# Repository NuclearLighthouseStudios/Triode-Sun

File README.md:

# Triode Sun Tube Preamp

These are the KiCAD schematics and board layout filed for my Triode Sun Tube Preamp pedal.  
If you just want the Gerber files or a PDF of the schematic check out the releases tab for downloads.

This PCB should be easily manufacturable with most online PCB houses by just uploading the gerber files.

This board is designed to be used with my Switchboard Pedal IO PCB which you can find [here](https://github.com/NuclearLighthouseStudios/Switchboard).

## BOM

| Reference       | Quantity | Value  | Description                                          |
| :-------------- | -------: | -----: | :--------------------------------------------------- |
| C2 C4           | 2        | 470n   | WIMA MKS2 50V                                        |
| C1 C3 C5        | 3        | 100n   | WIMA MKS2 63V                                        |
| C6              | 1        | 1µ     | WIMA MKS2 50V                                        |
| J1              | 1        |        | Pin Header, 6 pins, 2.54mm spacing                   |
| J2              | 1        |        | DC Barrel Jack with internal switch                  |
| Q1 Q2           | 2        | BC547B | 0.1A Ic, 45V Vce, Small Signal NPN Transistor, TO-92 |
| R1 R2 R5 R9 R10 | 5        | 1M     | Metal film resistor 1%, DIN 0207                     |
| R3 R11          | 2        | 10k    | Metal film resistor 1%, DIN 0207                     |
| R4 R12          | 2        | 39k    | Metal film resistor 1%, DIN 0207                     |
| R6 R7           | 2        | 390K   | Metal film resistor 1%, DIN 0207                     |
| R8              | 1        | 100K   | Metal film resistor 1%, DIN 0207                     |
| RV1 RV2         | 2        | 100k   | Alps RK09K1130C94 Potentiometer                      |
| U1              | 1        | ECC82  | ECC82 / 17AU7 in noval print socket                  |

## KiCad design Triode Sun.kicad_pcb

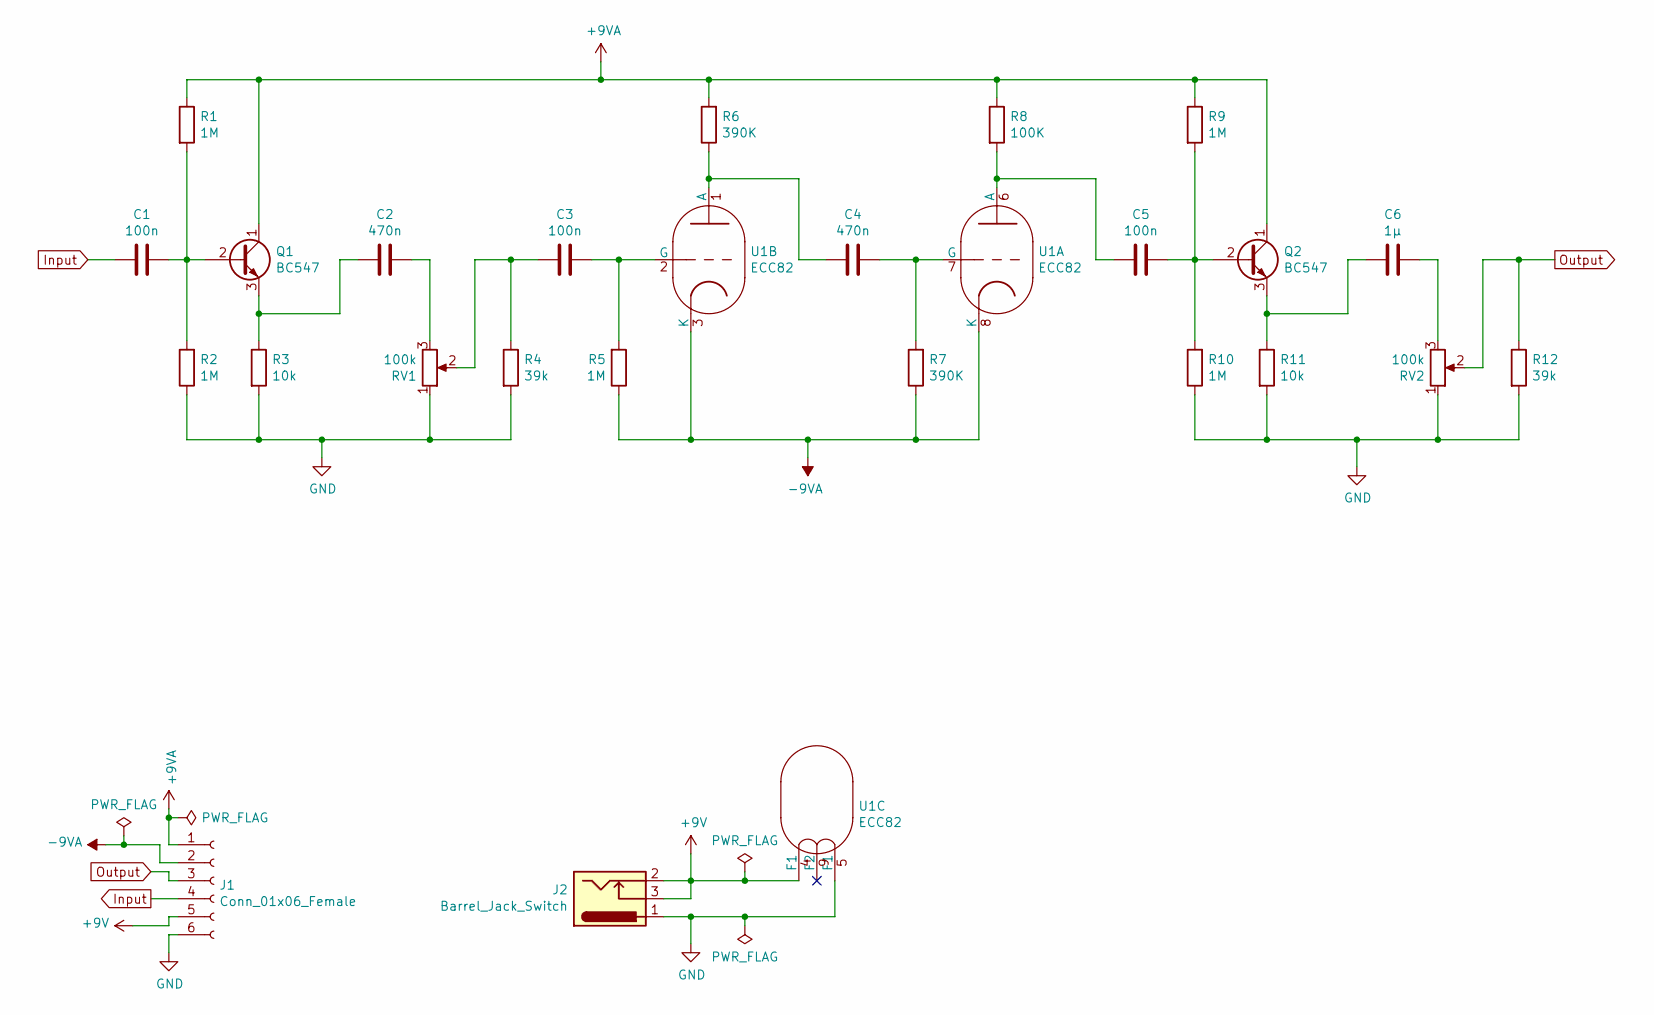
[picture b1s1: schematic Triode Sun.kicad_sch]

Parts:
C1, C3, C5: 100n; C_Rect_L7.2mm_W2.5mm_P5.00mm_FKS2_FKP2_MKS2_MKP2
C2, C4: 470n; C_Rect_L7.2mm_W3.5mm_P5.00mm_FKS2_FKP2_MKS2_MKP2
C6: 1µ; C_Rect_L7.2mm_W4.5mm_P5.00mm_FKS2_FKP2_MKS2_MKP2
J1: Conn_01x06_Female; PinHeader_1x06_P2.54mm_Vertical
J2: Barrel_Jack_Switch; BarrelJack_Horizontal_Short
Q1, Q2: BC547; TO-92_Wide
R1, R2, R5, R9, R10: 1M; R_Axial_DIN0207_L6.3mm_D2.5mm_P2.54mm_Vertical
R3, R11: 10k; R_Axial_DIN0207_L6.3mm_D2.5mm_P2.54mm_Vertical
R4, R12: 39k; R_Axial_DIN0207_L6.3mm_D2.5mm_P2.54mm_Vertical
R6, R7: 390K; R_Axial_DIN0207_L6.3mm_D2.5mm_P2.54mm_Vertical
R8: 100K; R_Axial_DIN0207_L6.3mm_D2.5mm_P2.54mm_Vertical
RV1, RV2: 100k; Potentiometer_Alps_RK09K_Single_Vertical
U1: ECC82; SOCKET-NOVAL

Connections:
+9V: J1.5, J2.2, J2.3, U1.4 (F1)
+9VA: J1.1, Q1.1 (C), Q2.1 (C), R1.1, R6.2, R8.1, R9.1
-9VA: J1.2, R5.1, R7.1, U1.3 (K), U1.8 (K)
GND: J1.6, J2.1, R2.1, R3.2, R4.2, R10.1, R11.2, R12.2, RV1.1, RV2.1, U1.5 (F1)
Input: C1.2, J1.4
unnamed: C1.1, Q1.2 (B), R1.2, R2.2
unnamed: C2.1, RV1.3
unnamed: C2.2, Q1.3 (E), R3.1
unnamed: C3.1, R5.2, U1.2 (G)
unnamed: C3.2, R4.1, RV1.2
unnamed: C4.1, R7.2, U1.7 (G)
unnamed: C4.2, R6.1, U1.1 (A)
unnamed: C5.1, Q2.2 (B), R9.2, R10.2
unnamed: C5.2, R8.2, U1.6 (A)
unnamed: C6.1, RV2.3
unnamed: C6.2, Q2.3 (E), R11.1
Output: J1.3, R12.1, RV2.2

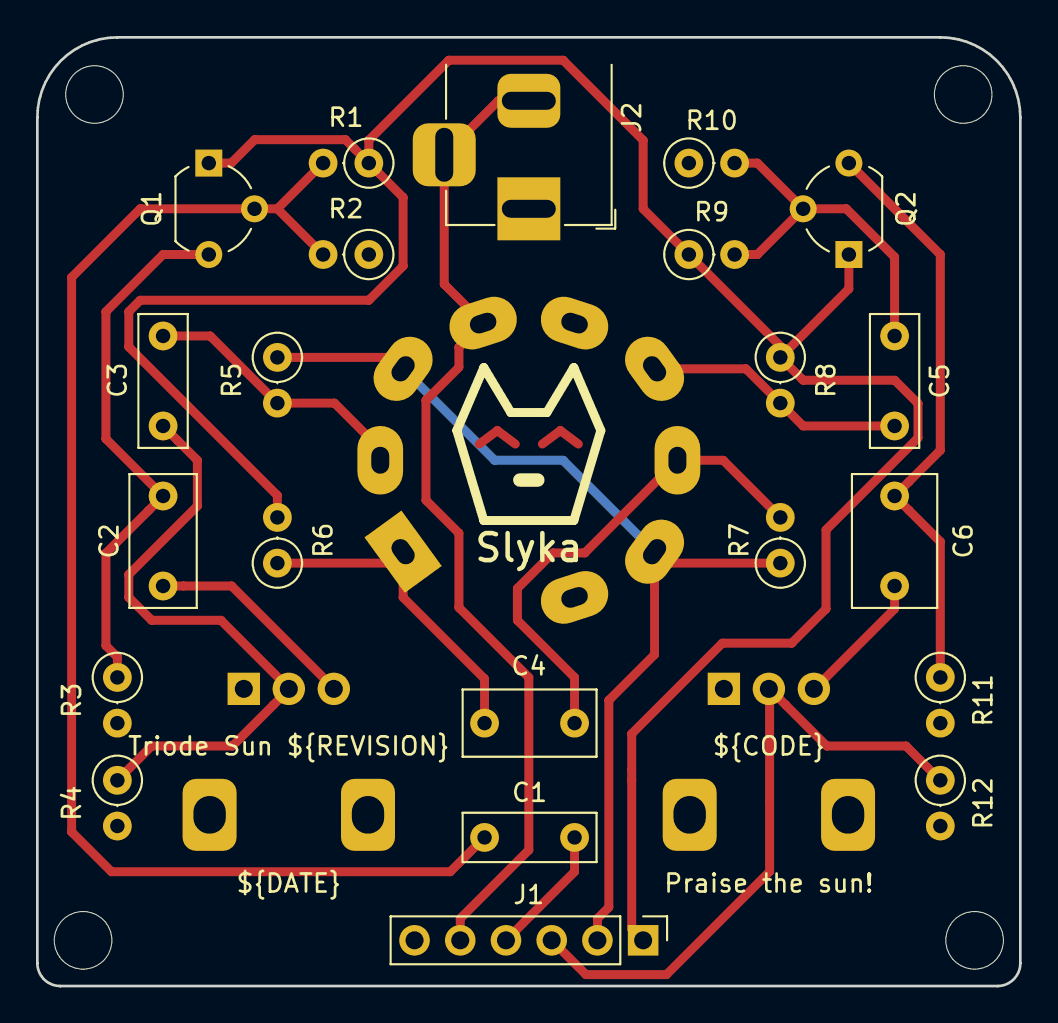
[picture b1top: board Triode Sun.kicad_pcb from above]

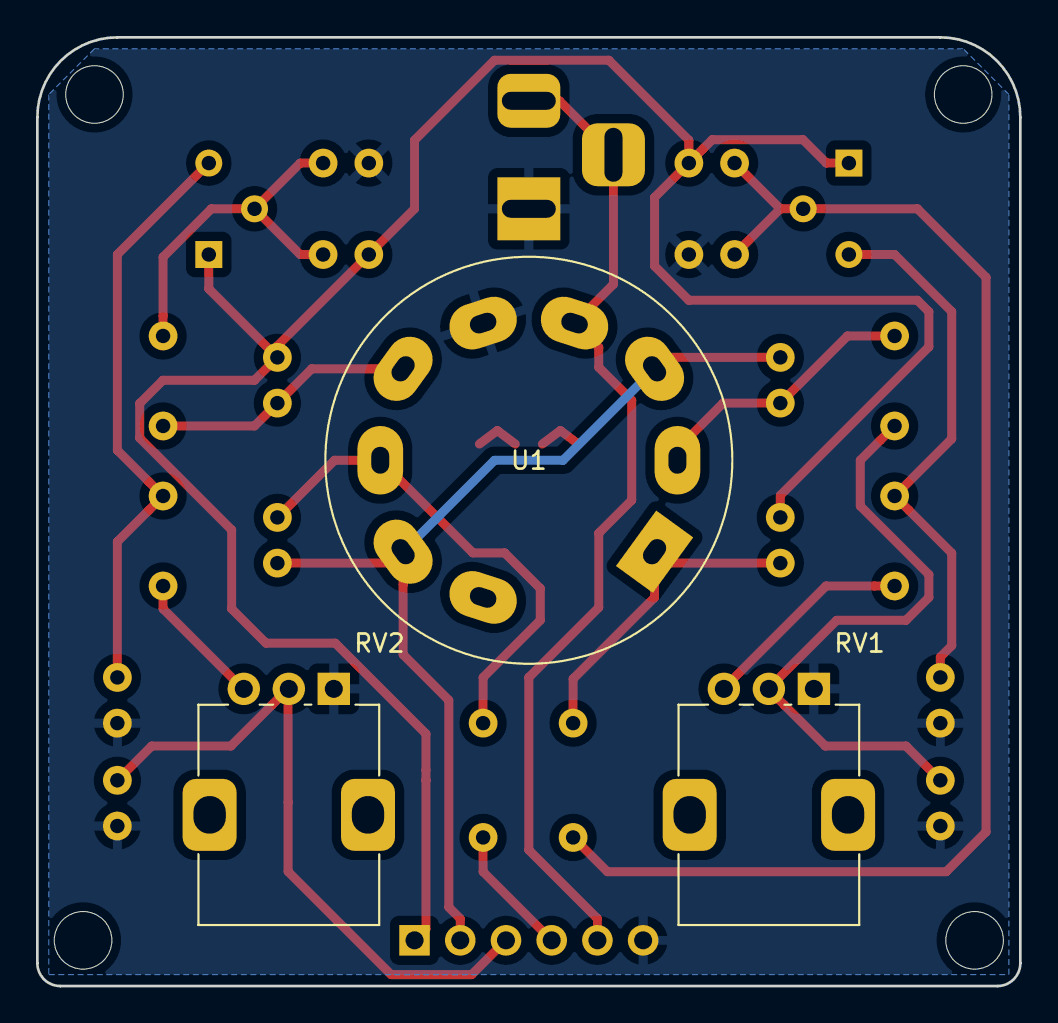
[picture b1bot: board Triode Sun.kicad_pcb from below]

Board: 2 copper layers, 54.6 x 52.7 mm, 25 parts (3 on the bottom side), 17 nets.

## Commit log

2020-09-28 Public release! Yay!
2020-12-30 Add readme with BOM! Yay!
2020-12-31 Fix cap voltages
2022-01-21 Migrate to KiCAD 6
2022-08-14 Update footprints and libraries
2022-08-14 Fix DRC errors

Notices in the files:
parts and their libraries:
LICENSE: CC BY-NC-SA
